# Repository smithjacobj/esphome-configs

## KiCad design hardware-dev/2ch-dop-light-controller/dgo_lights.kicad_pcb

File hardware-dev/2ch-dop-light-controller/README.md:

The files contained here are plans for a 2-channel 5v light controller using an ESP32-C3. They were
created in the free and open-source [KiCad](https://kicad.org)

Known issues:
* The solder lugs for the outputs are slightly too small for the tinned "YETOR" connectors listed
  below. I ended up just whittling a little solder and some strands off before insertion.
* The footprint for the fuse mounts are not accurate and require some bending. The fuse mounts used
  are [these](https://www.amazon.com/dp/B08GSG1FNV), which hold APM/ATM/"mini-ATO" style blade
  fuses.
* These fuses also don't come in 2.5A, so I ended up using 2A fuses. It's unlikely you'll overdraw
  with 3 strings per channel; 1 30-light string draws only about 600mA peak. It's more to kill power
  if something shorts out.
* The current design has no reverse polarity protection. Check and check again!
* The "YETOR" connector wire colors are opposite the polarity for the light strings I connected, so do your due diligence on determining polarity there as well. 

There is also an STL file, 7mm_cable_gland.stl, which I created and printed in a urethane resin to
create water-resistant fittings for the project box for the
["YETOR Waterproof Connectors 2 Wire"](https://www.amazon.com/dp/B07WDBLFDN) and power cord to enter
through. It's set for a 3/4" hole (large enough to fit the low voltage connector heads through).

This is an amateur design! Use at your own risk!

THE DESIGN IS PROVIDED "AS IS", WITHOUT WARRANTY OF ANY KIND, EXPRESS OR
IMPLIED, INCLUDING BUT NOT LIMITED TO THE WARRANTIES OF MERCHANTABILITY,
FITNESS FOR A PARTICULAR PURPOSE AND NONINFRINGEMENT. IN NO EVENT SHALL THE
AUTHORS OR COPYRIGHT HOLDERS BE LIABLE FOR ANY CLAIM, DAMAGES OR OTHER
LIABILITY, WHETHER IN AN ACTION OF CONTRACT, TORT OR OTHERWISE, ARISING FROM,
OUT OF OR IN CONNECTION WITH THE DESIGN OR THE USE OR OTHER DEALINGS IN THE
DESIGN.

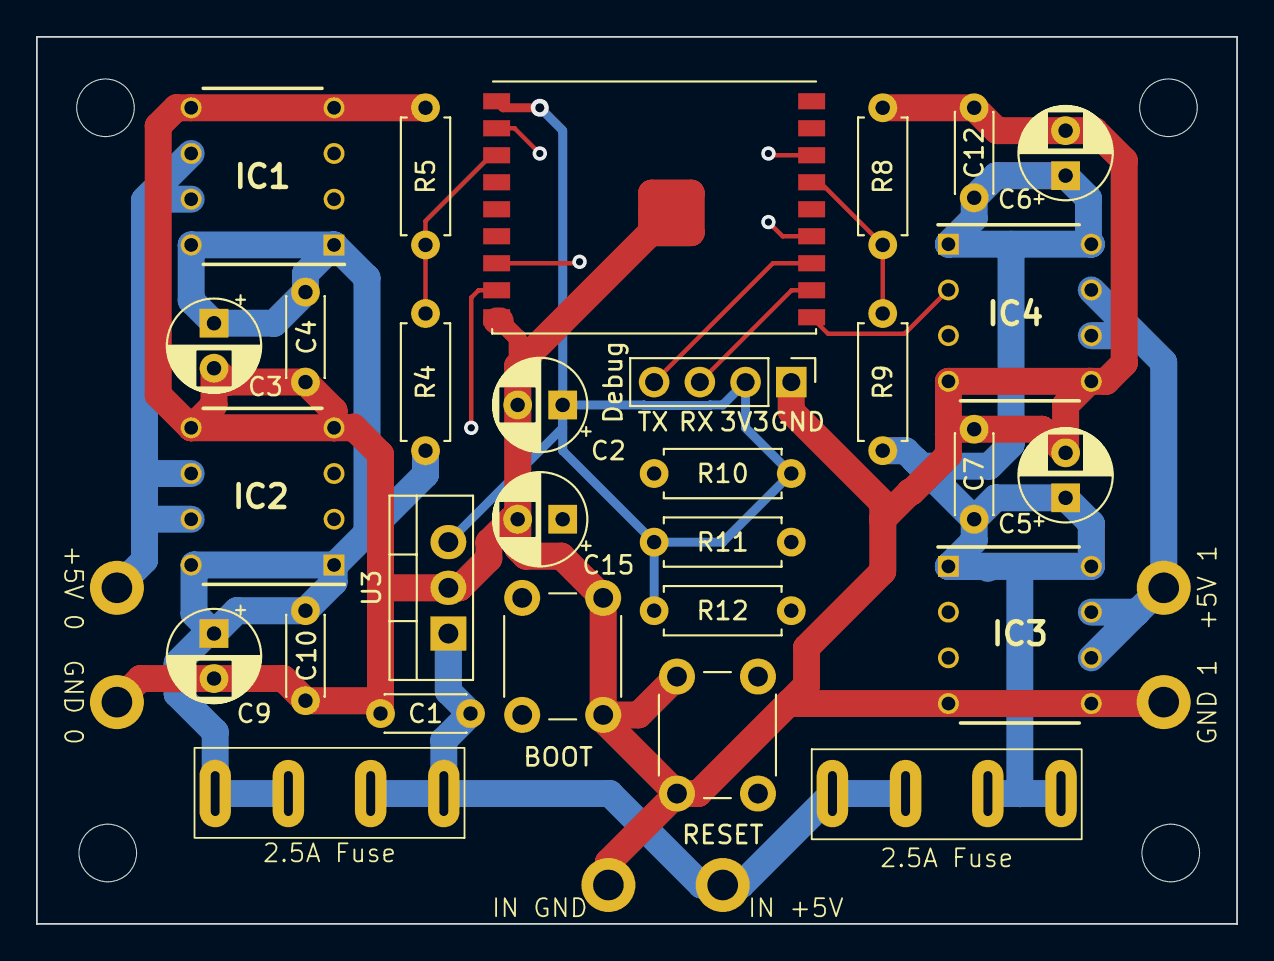
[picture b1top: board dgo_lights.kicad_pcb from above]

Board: 4 copper layers, 66.7 x 49.3 mm, 35 parts (0 on the bottom side), 17 nets.

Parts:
2.5A Fuse, 2.5A Fuse#2: 2.5A; ATO Fuse Holder
+5V 0: OUT 0; 14GA Wire Pad
+5V 1: OUT 1; 14GA Wire Pad
BOOT: BOOT; SW_PUSH_6mm
C1: 100nF; C_Disc_D4.3mm_W1.9mm_P5.00mm
C2: 10uF; CP_Radial_D5.0mm_P2.50mm
C3, C5, C6, C9, C15: 1uF; CP_Radial_D5.0mm_P2.50mm
C4, C7, C10, C12: 0.1uF Ceramic; C_Disc_D4.3mm_W1.9mm_P5.00mm
Debug: Debug; PinHeader_1x04_P2.54mm_Vertical
GND 0: GND 0; 14GA Wire Pad
GND 1: GND 1; 14GA Wire Pad
IC1, IC2, IC3, IC4: MCP1406-E_P; MCP1406-PDIP
IN +5V: +5V; 14GA Wire Pad
IN GND: GND; 14GA Wire Pad
R4, R9, R10, R11, R12: 10kΩ; R_Axial_DIN0207_L6.3mm_D2.5mm_P7.62mm_Horizontal
R5, R8: 2.5kΩ; R_Axial_DIN0207_L6.3mm_D2.5mm_P7.62mm_Horizontal
RESET: RESET; SW_PUSH_6mm
U1: ESP32-C3-WROOM-02
U3: LF33_TO220; TO-220-3_Vertical

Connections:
/Ch0 Logic: IC1.2 (INPUT), IC2.2 (INPUT), U1.13 (GPIO18/USB_D-)
/Ch1 Logic: IC3.2 (INPUT), IC4.2 (INPUT), U1.10 (GPIO10)
/Fuse Sensor 0: R4.2, R5.1, U1.3 (GPIO4/ADC1_CH4)
/Fuse Sensor 1: R8.1, R9.1, U1.15 (GPIO3/ADC1_CH3)
unnamed: BOOT.2, C1.2, C2.2, C3.2, C4.2, C5.2, C6.2, C7.2, C9.2, C10.2, C12.2, C15.2, Debug.1, GND 0.1, GND 1.1, IC1.4 (GND_1), IC1.5 (GND_2), IC2.4 (GND_1), IC2.5 (GND_2), IC3.4 (GND_1), IC3.5 (GND_2), IC4.4 (GND_1), IC4.5 (GND_2), IN GND.1, R5.2, R8.2, RESET.1, U1.9 (GND), U1.19 (GND), U3.2 (GND)
unnamed: 2.5A Fuse#2.2, C3.1, C4.1, C9.1, C10.1, IC1.1 (VDD_1), IC1.8 (VDD_2), IC2.1 (VDD_1), IC2.8 (VDD_2), R4.1
unnamed: +5V 0.1, IC1.6 (~OUT_1), IC1.7 (~OUT_2), IC2.6 (~OUT_1), IC2.7 (~OUT_2)
unnamed: 2.5A Fuse.2, C5.1, C6.1, C7.1, C12.1, IC3.1 (VDD_1), IC3.8 (VDD_2), IC4.1 (VDD_1), IC4.8 (VDD_2), R9.2
unnamed: +5V 1.1, IC3.6 (~OUT_1), IC3.7 (~OUT_2), IC4.6 (~OUT_1), IC4.7 (~OUT_2)
unnamed: C2.1, Debug.2, R10.2, R11.1, R12.1, U1.1 (3V3), U3.3 (VO)
unnamed: Debug.3, U1.11 (GPIO20/U0RXD)
unnamed: Debug.4, U1.12 (GPIO21/U0TXD)
unnamed: C15.1, R10.1, RESET.2, U1.2 (EN/CHIP_PU)
unnamed: R11.2, U1.16 (GPIO2/ADC1_CH2)
unnamed: R12.2, U1.7 (GPIO8)
unnamed: BOOT.1, U1.8 (GPIO9)
unnamed: 2.5A Fuse.1, 2.5A Fuse#2.1, C1.1, IN +5V.1, U3.1 (VI)

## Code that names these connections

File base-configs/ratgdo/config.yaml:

---
substitutions:
  uart_tx_pin: GPIO3
  uart_rx_pin: GPIO2
  input_obst_pin: GPIO4
  status_door_pin: GPIO5 # not used
  status_obstruction_pin: GPIO6 # not used
  dry_contact_open_pin: GPIO7 # not used
  dry_contact_close_pin: GPIO8 # not used
  dry_contact_light_pin: GPIO9 # not used

web_server:

esphome:
  name: ${id_prefix}
  friendly_name: ${friendly_name}
  project:
    name: ratgdo.esphome
    version: "2.5"

dashboard_import:
  package_import_url: github://ratgdo/esphome-ratgdo/v25board_esp32_d1_mini.yaml@main

packages:
  remote_package:
    url: https://github.com/ratgdo/esphome-ratgdo
    files: [base.yaml]
    refresh: 1s
  esp32-c3: !include ../../board-configs/esp32-c3-arduino.yaml

# Sync time with Home Assistant.
time:
  - platform: homeassistant
    id: homeassistant_time

api:
  id: api_server

improv_serial:

wifi:
  networks:
    <<: !secret WIFI_NETWORKS

logger:

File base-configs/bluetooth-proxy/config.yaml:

substitutions:
  CH0_PIN: GPIO18
  CH0_FAULT_PIN: GPIO4

  CH1_PIN: GPIO10
  CH1_FAULT_PIN: GPIO3

packages:
  esp32-c3: !include ../../board-configs/esp32-c3.yaml

esphome:
  name: ${DEVICE_NAME}

logger:
  level: ${LOG_LEVEL}

wifi:
  networks:
    <<: !secret WIFI_NETWORKS
    
api:
ota:
bluetooth_proxy:

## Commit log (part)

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2023-12-11 Initial monorepo for esphome configs
2023-12-11 reorganizing and removing redundant esphome labeling
2023-12-14 lots of clean up
2023-12-14 Add hardware schematics to the repository
2023-12-14 Added cable gland STL file and updated readme
2023-12-15 Add more information for PCB
2023-12-15 Added second channel sensor and light
2023-12-18 Fixed rmt_channel issue
    Both light channels were on the same RMT channel causing both channels'
    lights to be affected by commands on either channel.
2023-12-20 Initial non-working build
2023-12-20 updated from clang-tidy and white always on bug
2023-12-27 fix emporia vue config
2023-12-27 add glimmer effect to dop-lights
2023-12-27 added delta-only updates to esp32_rmt_led_strip (has TODO)
2023-12-27 updated to add configurability to partial updates
2023-12-28 changed from abstract class to functor/lambda support
2023-12-29 added rwg effect to dop lights, formatting fixes from esphome repo
2024-01-02 porting RMT delay back to my config
2024-01-03 fixing bugs with RMT delay
2024-01-18 Add Emporia Vue config and duplicate for second unit
2024-01-22 Add Vue configs; doorbell stubs
2024-01-24 updated emporia vue schemas
2024-01-24 working on non-allocating speaker component
2024-03-21 added Easter effect to DOP lights and fixed timing for line capacitance
2024-06-05 made fan controller build
2024-06-05 Add an actual config for fan
2024-06-05 BT proxy test
2024-09-16 jyqd-v8.8b fan controller.
2024-09-16 removing jyqd-v8.8b fan controller
2024-09-16 updates to clang-format
2024-09-16 cleanup - remove kids room fan v1 config
2024-09-16 various configs
2024-10-08 added supermini wifi sensor burnin to test supposed failures of supermini
2024-10-08 updated dop-lights to work with 2024.09.*
2024-10-08 ratgdo configs
2024-11-24 Add Five Color Random effect, plus some old bugfixes that didn't get committed
2025-02-09 lvdc switch e.g. for arcade1up locking
2025-07-03 Added Indiana Jones XL9535 'darts' config
2025-07-24 update to allow looping of blowgun sim
2025-07-30 Added random Indy darts XL9535 configuration
2026-01-06 updated emporia vue configs
